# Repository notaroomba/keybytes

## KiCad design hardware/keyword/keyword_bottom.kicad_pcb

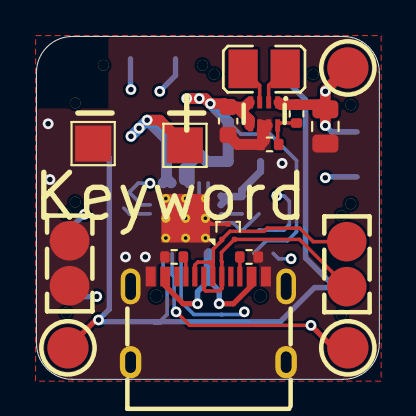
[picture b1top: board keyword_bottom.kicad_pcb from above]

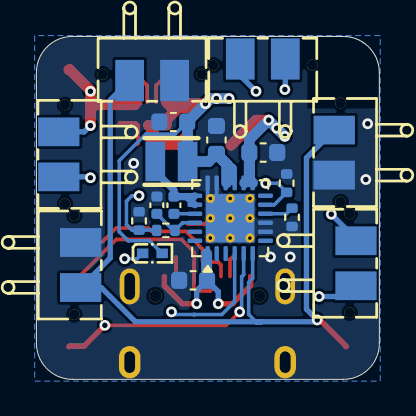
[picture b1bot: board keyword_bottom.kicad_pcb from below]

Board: 4 copper layers, 19.1 x 19.0 mm, 36 parts (19 on the bottom side), 20 nets.

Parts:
C16: 1uF; C_0603_1608Metric
C17: 4.7uF; C_0402_1005Metric
C18, C20, C23: 10uF; C_0603_1608Metric
C19: 47nF; C_0402_1005Metric
C21: 22uF; C_0603_1608Metric
C22: 47uF; C_0805_2012Metric
CN2, CN3, CN4: YZ00615050R-08; TESTPOINT-SMD_BD2.0-H5.0
R1, R2: 5.1K; R_0402_1005Metric
R4: 260R; R_0402_1005Metric
R5: 5.23K; R_0402_1005Metric
R6: 30.1K; R_0402_1005Metric
R7: 10K; R_0402_1005Metric
R9: 511K; R_0402_1005Metric
R10: 91K; R_0402_1005Metric
TP4: BATP; TestPoint_Pad_2.0x2.0mm
TP5: BATN; TestPoint_Pad_2.0x2.0mm
U2: TPD2EUSB30; Texas_DRT-3
U4, U5, U6, U7, U13, U15: YZ13515055F-02025-02; CONN-SMD_YZ13515055F-02025-02
U8: BQ25895RTW; Texas_RTW_WQFN-24-1EP_4x4mm_P0.5mm_EP2.7x2.7mm_ThermalVias
U9: DFE252012P-1R0M=P2; L1008
U16: XRTC252012S2R2MBCA; IND-SMD_L2.5-W2.0-B
U17: SZYY0402Y_C434450; LED0402-FD_YELLOW
U18: TPS631000DRLR; SOT-583-8_L2.1-W1.2-P0.50-LS1.6-BL
U19, U20: YZ37215050R-02025-05; SMD_2P_YZ37215050R-02025-05
USB1: TYPE-C 16PIN 2MD(073); USB-C-SMD_TYPE-C-6PIN-2MD-073

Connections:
+3.3V: C22.1, CN2.1, R9.2, U4.1, U6.1, U13.1, U18.1 (VOUT)
/DN: U2.1 (D+), U19.2, USB1.5 (DN2), USB1.7 (DN1)
/DP: U2.2 (D-), U19.1, USB1.6 (DP1), USB1.8 (DP2)
/SCL: CN4.1, U5.1, U7.1, U8.6 (SDA), U15.1
/SDA: CN3.1, U4.2, U6.2, U8.5 (SCL), U13.2
GND: C16.2, C17.2, C18.2, C20.2, C21.2, C22.2, C23.2, R1.2, R2.2, R4.2, R6.2, R7.2, R10.1, TP5.1, U2.3 (GND), U5.2, U7.2, U8.8 (OTG), U8.9 (~CE), U8.17 (PGND), U8.18 (PGND), U8.25 (PGND), U15.2, U18.6 (MODE), U18.7 (GND), U20.1, U20.2, USB1.1 (GND), USB1.12 (GND), USB1.13 (SHELL), USB1.14 (SHELL)
unnamed: C18.1, TP4.1, U8.13 (BAT), U8.14 (BAT)
unnamed: C19.1, U8.19 (SW), U8.20 (SW), U16.1
unnamed: C19.2, U8.21 (BTST)
unnamed: R4.1, U8.10 (ILIM)
unnamed: C17.1, R5.1, U8.22 (REGN)
unnamed: R5.2, R6.1, R7.1, U8.11 (TS)
unnamed: U8.4 (STAT), U17.2 (K)
unnamed: R9.1, R10.2, U18.8 (FB)
unnamed: U9.2, U18.3 (LX1)
unnamed: U9.1, U18.2 (LX2)
unnamed: R1.1, USB1.4 (CC1)
unnamed: R2.1, USB1.10 (CC2)
VBUS: C16.1, U8.1 (VBUS), USB1.2 (VBUS), USB1.11 (VBUS)
VCC: C20.1, C21.1, C23.1, U8.15 (SYS), U8.16 (SYS), U16.2, U17.1 (A), U18.4 (VIN), U18.5 (EN)

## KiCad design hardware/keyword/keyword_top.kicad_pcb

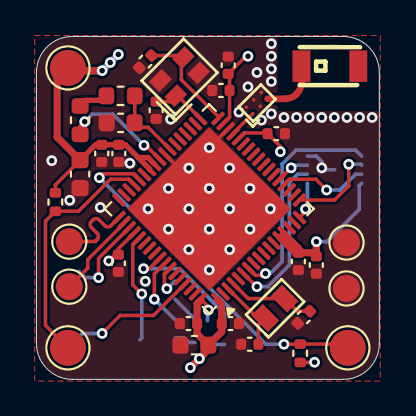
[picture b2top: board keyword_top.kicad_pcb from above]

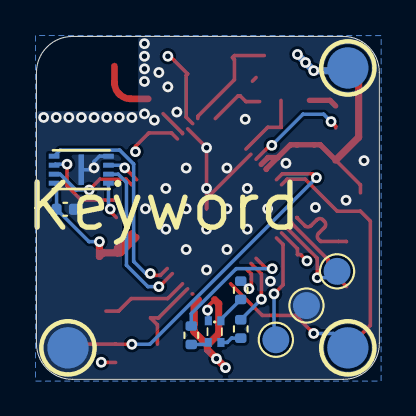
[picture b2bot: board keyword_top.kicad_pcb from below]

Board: 4 copper layers, 19.1 x 19.0 mm, 45 parts (12 on the bottom side), 30 nets.

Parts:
AE1: 2450AT18A100E; ANT-SMD_L3.2-W1.6
C1, C2, C6, C9: 10pF; C_0402_1005Metric
C3, C25, C26, C27, C29, C30, C32, C34, C35: 100nF; C_0402_1005Metric
C24, C28, C31: 4.7uF; C_0603_1608Metric
C33, C36: 1uF; C_0402_1005Metric
CN1, CN5, CN6: YZ00615050R-08; TestPoint_Pad_D2.0mm
CN7, CN8, CN9: YZ00615050R-08; TESTPOINT-SMD_BD2.0-H5.0
L1: 10uH; L_0603_1608Metric
L2: 10nH; L_0603_1608Metric
R8, R11: 4.7K; R_0402_1005Metric
R12, R13, R14: 100R; R_0402_1005Metric
TP1, TP2, TP3, TP6, TP7, TP8, TP9: TestPoint; TestPoint_Pad_D1.5mm
U3: NX2012SA-32.768KHZ-STD-MUB-2; CRYSTAL-SMD_L2.0-W1.2
U10: W25Q16JVUXIQ; USON-8_L3.0-W2.0-P0.50-BL-EP
U11: STM32WB55RGVx; QFN-68-1EP_8x8mm_P0.4mm_EP6.4x6.4mm
U12: MLPF-WB-04D3; CSPG-6_L1.6-W1.0-P0.50-TL_MLPF-WB-04D3
U14: XL-1608RGBC; LED-SMD_4P-L1.6-W0.8-BL
X1: NX2016SA-32MHZ-STD-CZS-5; OSC-SMD_4P-L2.0-W1.6-BL

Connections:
+3.3V: C3.1, C25.1, C26.1, C27.1, C28.1, C29.1, C30.1, C31.1, C32.1, C33.1, C34.1, C35.1, C36.1, CN1.1, CN7.1, R8.2, R11.2, U10.8 (VCC), U11.1 (VBAT), U11.13 (VREF+), U11.14 (VDDA), U11.30 (VDD), U11.33 (VDDRF), U11.44 (VDDSMPS), U11.45 (VDD), U11.55 (VDDUSB), U11.68 (VDD), U14.3 (com)
/BB_SWIO: CN8.1, U11.65 (PB5)
/DN: TP6.1, U11.52 (PA11)
/DP: TP7.1, U11.53 (PA12)
/FLASH_CLK: U10.6 (CLK), U11.18 (PA3)
/FLASH_IO0: U10.5 (DI(IO0)), U11.7 (PB9)
/FLASH_IO1: U10.2 (DO(IO1)), U11.6 (PB8)
/FLASH_IO2: U10.3 (WP#(IO2)), U11.22 (PA7)
/FLASH_IO3: U10.7 (HOLD#orRESET#(IO3)), U11.21 (PA6)
/FLASH_NCS: U10.1 (~CS), U11.17 (PA2)
/HXIN: C1.1, U11.35 (OSC_IN), X1.1
/HXOUT: C2.1, U11.34 (OSC_OUT), X1.3
/LXIN: C6.1, U3.1 (OSC1), U11.3 (PC14)
/LXOUT: C9.1, U3.2 (OSC2), U11.4 (PC15)
/RF: U11.31 (RF1), U12.A1 (IN)
/SCL: CN6.1, R8.1, U11.47 (PB13)
/SDA: CN5.1, R11.1, U11.48 (PB14)
/STATUS_B: R14.2, U11.60 (PC12)
/STATUS_G: R12.2, U11.61 (PD0)
/STATUS_R: R13.1, U11.62 (PD1)
/SWCLK: TP2.1, U11.56 (PA14)
/SWDIO: TP1.1, U11.54 (PA13)
GND: C1.2, C2.2, C3.2, C6.2, C9.2, C24.2, C25.2, C26.2, C27.2, C28.2, C29.2, C30.2, C31.2, C32.2, C33.2, C34.2, C35.2, C36.2, CN9.1, TP3.1, TP8.1, TP9.1, U10.4 (GND), U10.9 (EP), U11.32 (VSSRF), U11.42 (VSSSMPS), U11.69 (VSS), U12.A2 (GND4), U12.B1 (GND3), U12.B2 (GND2), U12.B3 (GND1), X1.2 (GND), X1.4 (GND)
unnamed: AE1.1 (ANT), U12.A3 (OUT)
unnamed: L1.1, L2.2
unnamed: R12.1, U14.2
unnamed: R13.2, U14.1
unnamed: R14.1, U14.4
unnamed: C24.1, L1.2, U11.41 (VFBSMPS)
unnamed: L2.1, U11.43 (VLXSMPS)
